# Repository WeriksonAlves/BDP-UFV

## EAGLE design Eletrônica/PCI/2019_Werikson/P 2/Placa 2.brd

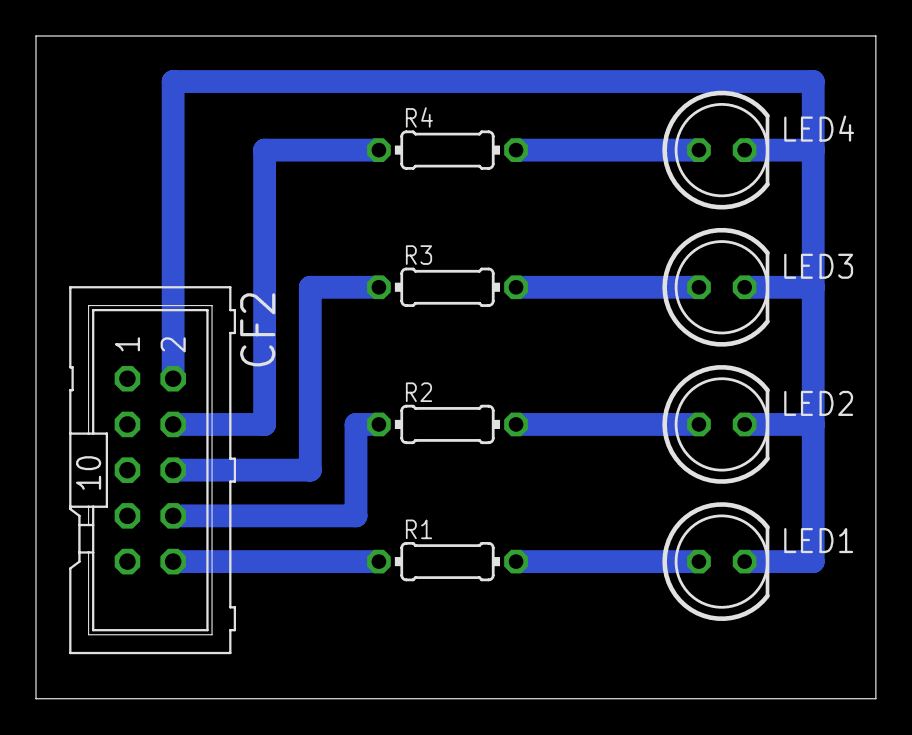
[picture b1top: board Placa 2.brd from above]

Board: 2 copper layers, 46.7 x 36.8 mm, 9 parts (0 on the bottom side), 9 nets.

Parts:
CF2: ML10
LED1, LED2, LED3, LED4: LED5MM
R1, R2, R3, R4: 220; 0204/7

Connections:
GND: CF2.2, LED1.K, LED2.K, LED3.K, LED4.K
unnamed: LED1.A, R1.2
unnamed: LED2.A, R2.2
unnamed: LED3.A, R3.2
unnamed: LED4.A, R4.2
unnamed: CF2.10, R1.1
unnamed: CF2.8, R2.1
unnamed: CF2.6, R3.1
unnamed: CF2.4, R4.1

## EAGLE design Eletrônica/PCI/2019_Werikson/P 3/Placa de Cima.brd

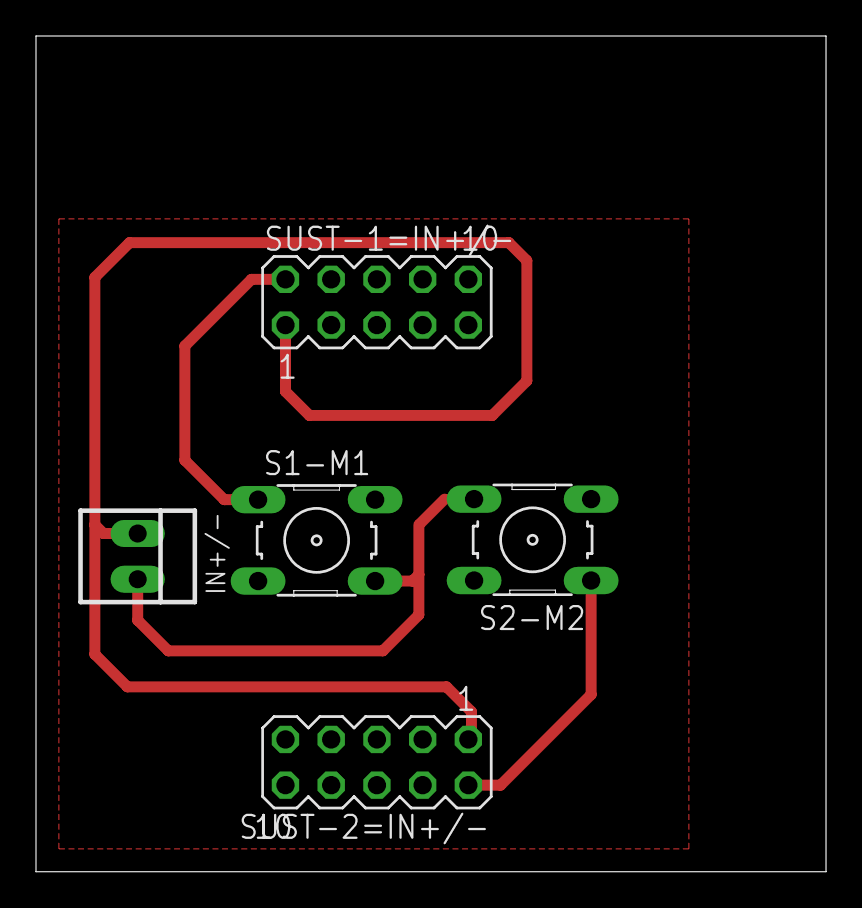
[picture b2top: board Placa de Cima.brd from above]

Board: 2 copper layers, 43.9 x 46.4 mm, 5 parts (0 on the bottom side), 4 nets.

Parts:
IN+/-: 22-23-2021
S1-M1, S2-M2: B3F-10XX
SUST-1=IN+/-, SUST-2=IN+/-: MA05-2

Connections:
GND: IN+/-.1, SUST-1=IN+/-.1, SUST-2=IN+/-.1
unnamed: S1-M1.1, SUST-1=IN+/-.2
unnamed: S2-M2.1, SUST-2=IN+/-.2
unnamed: IN+/-.2, S1-M1.4, S2-M2.4

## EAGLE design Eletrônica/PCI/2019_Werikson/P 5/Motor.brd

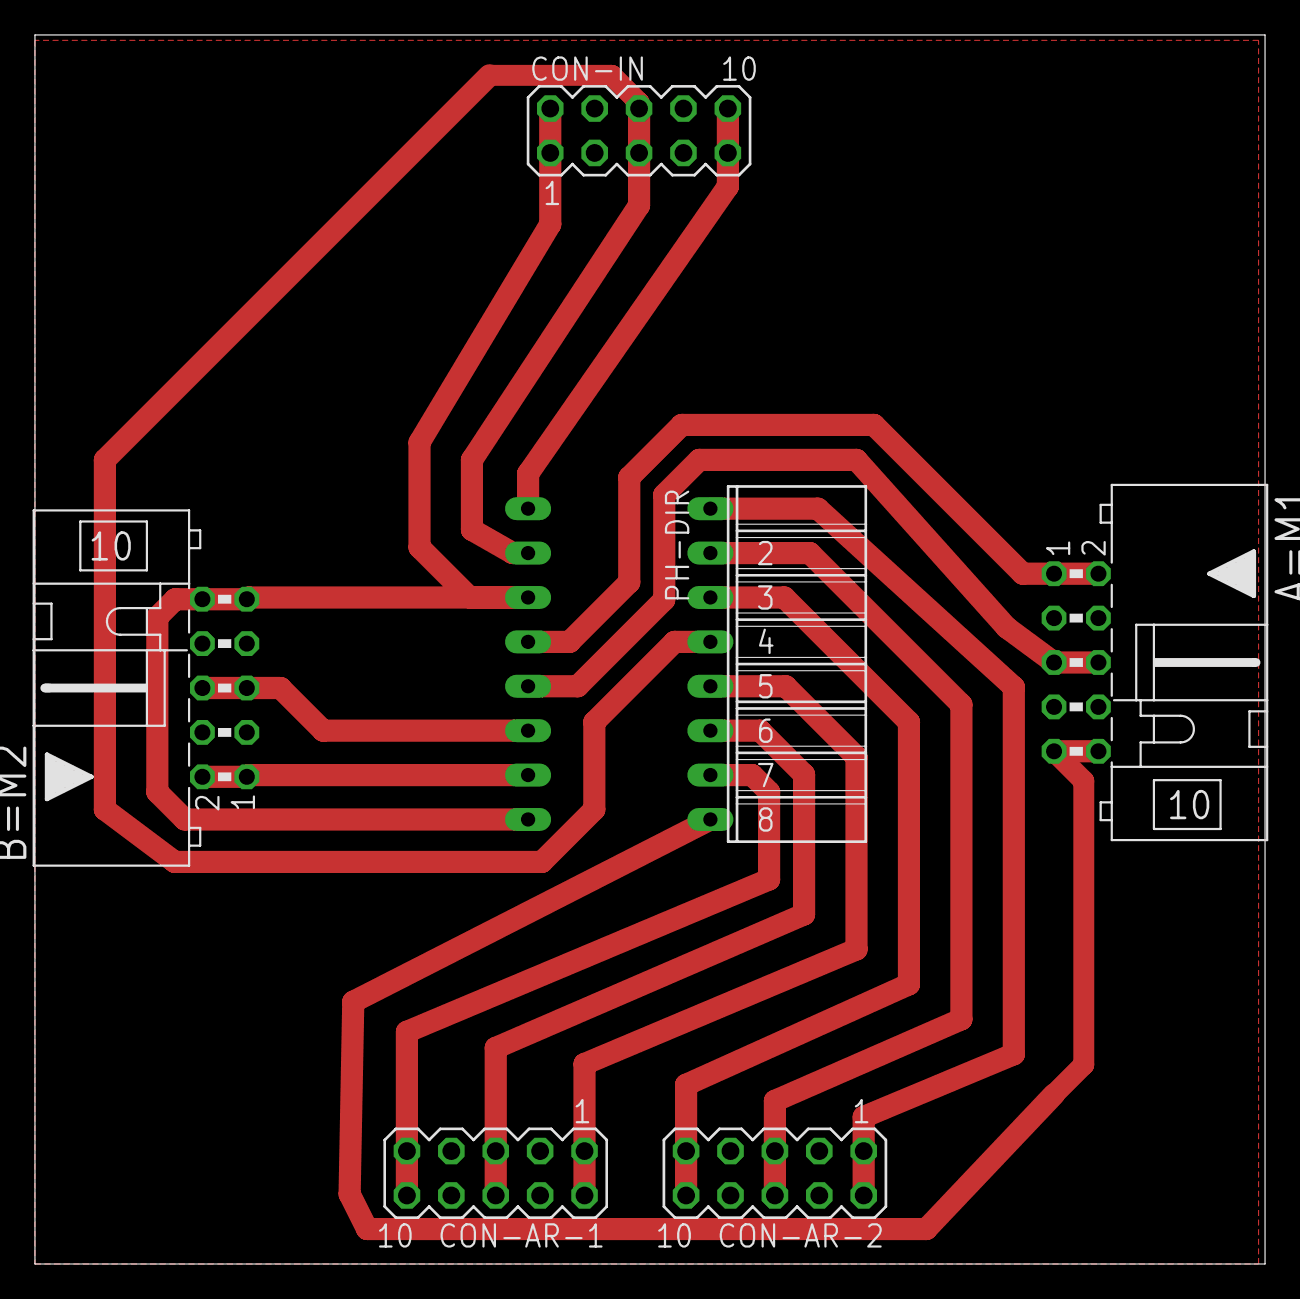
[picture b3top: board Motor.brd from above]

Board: 2 copper layers, 70.4 x 70.3 mm, 7 parts (1 on the bottom side), 13 nets.

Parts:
A=M1: ML10L
B=M2: ML10L
CON-AR-1, CON-AR-2: MA05-2
CON-IN: MA05-2
PH-DIR: FE08W
PH-ESQ: FE08W

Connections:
5V: CON-IN.5, CON-IN.6, PH-DIR.4, PH-ESQ.2
D5: CON-AR-2.1, CON-AR-2.2, PH-DIR.1
D6: CON-AR-1.9, CON-AR-1.10, PH-DIR.7
D7: CON-AR-1.5, CON-AR-1.6, PH-DIR.6
D8: CON-AR-1.1, CON-AR-1.2, PH-DIR.5
GND: A=M1.9, A=M1.10, B=M2.9, B=M2.10, CON-IN.1, CON-IN.2, PH-DIR.8, PH-ESQ.3, PH-ESQ.8
M1-1: A=M1.1, A=M1.2, PH-ESQ.4
M1-2: A=M1.5, A=M1.6, PH-ESQ.5
M2-1: B=M2.1, B=M2.2, PH-ESQ.7
M2-2: B=M2.5, B=M2.6, PH-ESQ.6
RX0: CON-AR-2.5, CON-AR-2.6, PH-DIR.2
TX1: CON-AR-2.9, CON-AR-2.10, PH-DIR.3
V0: CON-IN.9, CON-IN.10, PH-ESQ.1

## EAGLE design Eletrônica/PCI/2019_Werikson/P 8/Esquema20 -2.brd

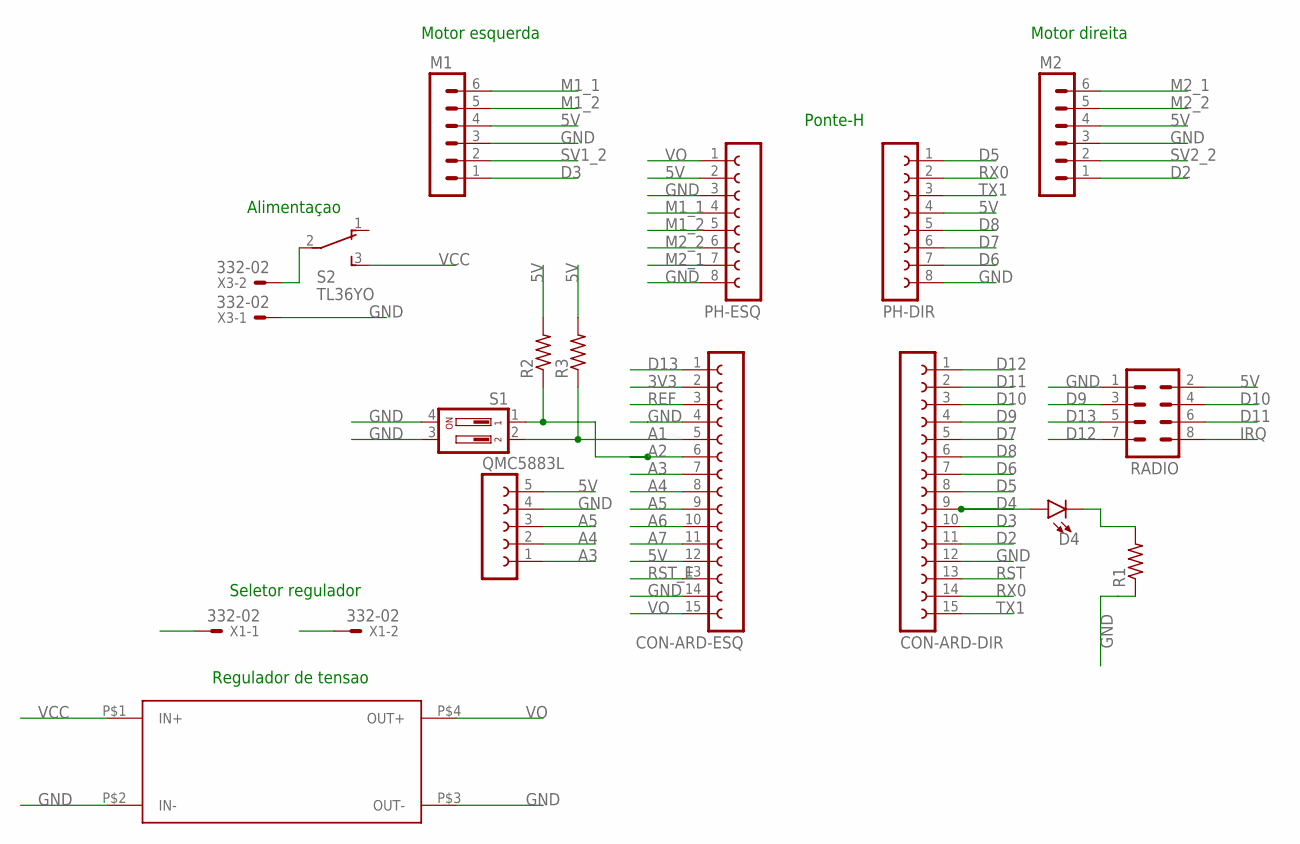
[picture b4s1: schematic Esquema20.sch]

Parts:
CON-ARD-DIR: FE15-1; FE15
CON-ARD-ESQ: FE15-1; FE15
D4: LED-3MM-NO_SILK; LED_3MM-NS
M1, M2: MA06-1
PH-DIR: FE08-1; FE08
PH-ESQ: FE08-1; FE08
QMC5883L: FE05W
R1, R2, R3: R-US_0207/12; 0207/12
RADIO: MA04-2
S1: DA02; DA-02
S2: TL36YO; TL3XYO
U$1: REGULADOR; REGULADOR-FP
X1, X3: 332-02

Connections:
3V3: CON-ARD-ESQ.2
5V: CON-ARD-ESQ.12, M1.4, M2.4, PH-DIR.4, PH-ESQ.2, QMC5883L.5, R2.2, R3.2, RADIO.2
A1: CON-ARD-ESQ.5, R3.1, S1.2
A2: CON-ARD-ESQ.6, R2.1, S1.1
A3: CON-ARD-ESQ.7, QMC5883L.1
A4: CON-ARD-ESQ.8, QMC5883L.2
A5: CON-ARD-ESQ.9, QMC5883L.3
A6: CON-ARD-ESQ.10; also elsewhere on the board
A7: CON-ARD-ESQ.11; also elsewhere on the board
D2: CON-ARD-DIR.11, M2.1
D3: CON-ARD-DIR.10, M1.1
D4: CON-ARD-DIR.9, D4.A
D5: CON-ARD-DIR.8, PH-DIR.1
D6: CON-ARD-DIR.7, PH-DIR.7
D7: CON-ARD-DIR.5, PH-DIR.6
D8: CON-ARD-DIR.6, PH-DIR.5
D9: CON-ARD-DIR.4, RADIO.3
D10: CON-ARD-DIR.3, RADIO.4
D11: CON-ARD-DIR.2, RADIO.6
D12: CON-ARD-DIR.1, RADIO.7
D13: CON-ARD-ESQ.1, RADIO.5
GND: CON-ARD-DIR.12, CON-ARD-ESQ.4, CON-ARD-ESQ.14, M1.3, M2.3, PH-DIR.8, PH-ESQ.3, PH-ESQ.8, QMC5883L.4, R1.1, RADIO.1, S1.3, S1.4, U$1.P$2 (IN-), U$1.P$3 (OUT-), X3.1; also elsewhere on the board
IRQ: RADIO.8
M1_1: M1.6, PH-ESQ.4
M1_2: M1.5, PH-ESQ.5
M2_1: M2.6, PH-ESQ.7
M2_2: M2.5, PH-ESQ.6
unnamed: S2.2, X3.2
unnamed: D4.K (C), R1.2
REF: CON-ARD-ESQ.3
RST: CON-ARD-DIR.13
RST_E: CON-ARD-ESQ.13
RX0: CON-ARD-DIR.14, PH-DIR.2
SV1_2: M1.2
SV2_2: M2.2
TX1: CON-ARD-DIR.15, PH-DIR.3
VCC: S2.3 (S), U$1.P$1 (IN+), X1.1; also elsewhere on the board
VO: CON-ARD-ESQ.15, PH-ESQ.1, U$1.P$4 (OUT+), X1.2

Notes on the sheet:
Motor direita
Motor esquerda
Alimentaçao
Ponte-H
Regulador de tensao
Seletor regulador

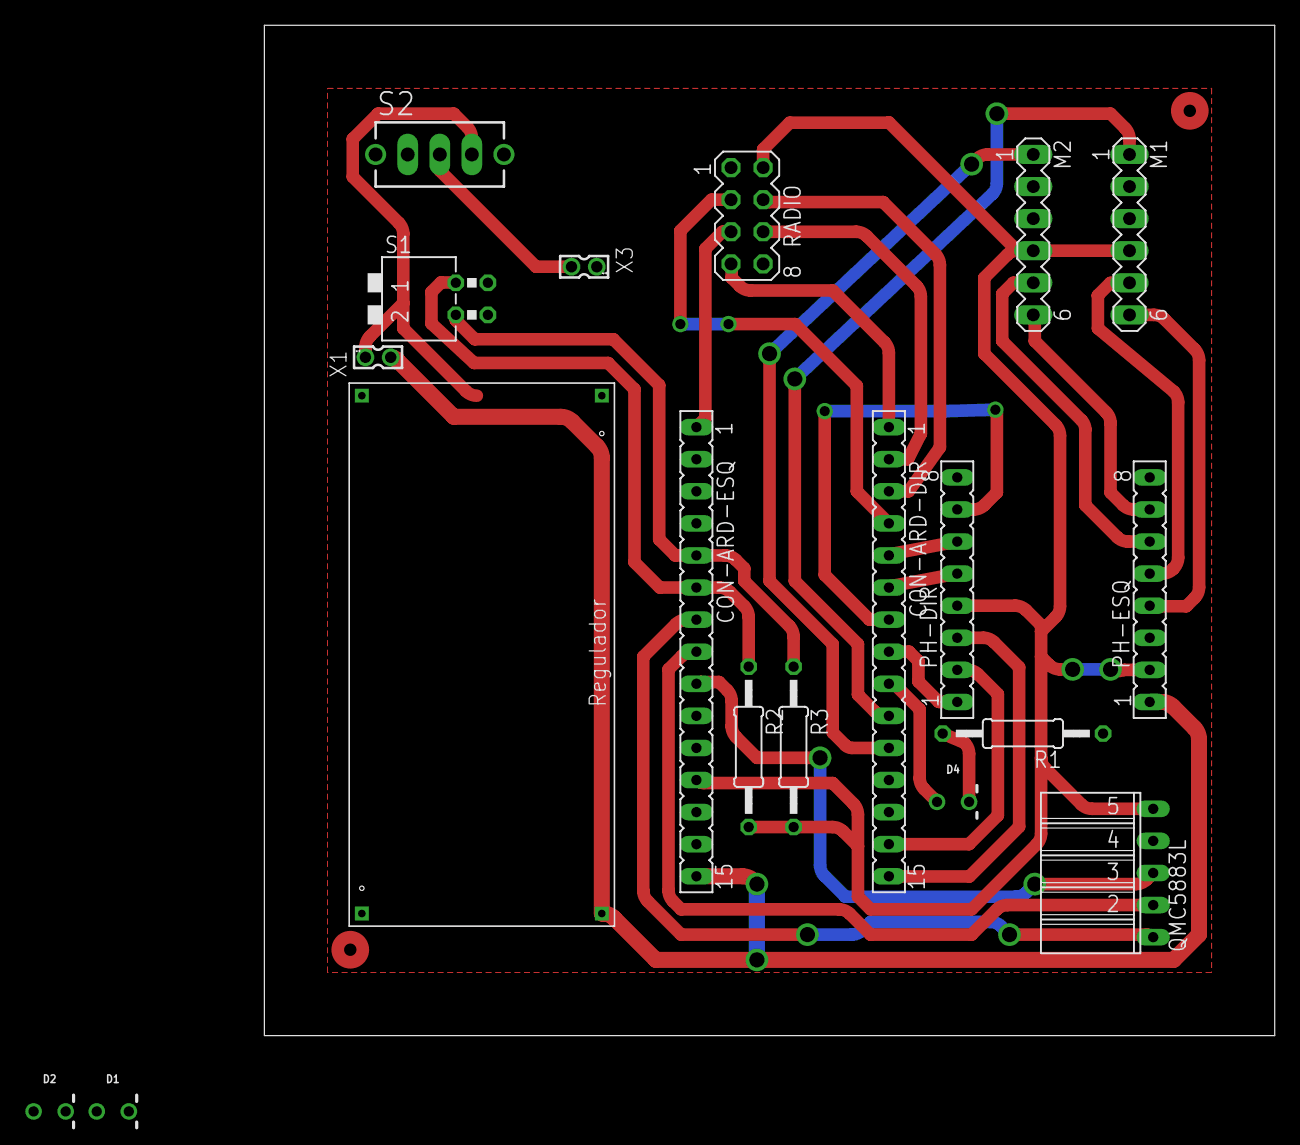
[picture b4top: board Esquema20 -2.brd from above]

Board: 2 copper layers, 80.0 x 80.0 mm, 19 parts (0 on the bottom side), 31 nets.

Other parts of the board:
D1, D2: LED_3MM-NS

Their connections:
A6: D1.K; also elsewhere on the board
A7: D2.A; also elsewhere on the board
GND: D2.K; also elsewhere on the board
VCC: D1.A; also elsewhere on the board

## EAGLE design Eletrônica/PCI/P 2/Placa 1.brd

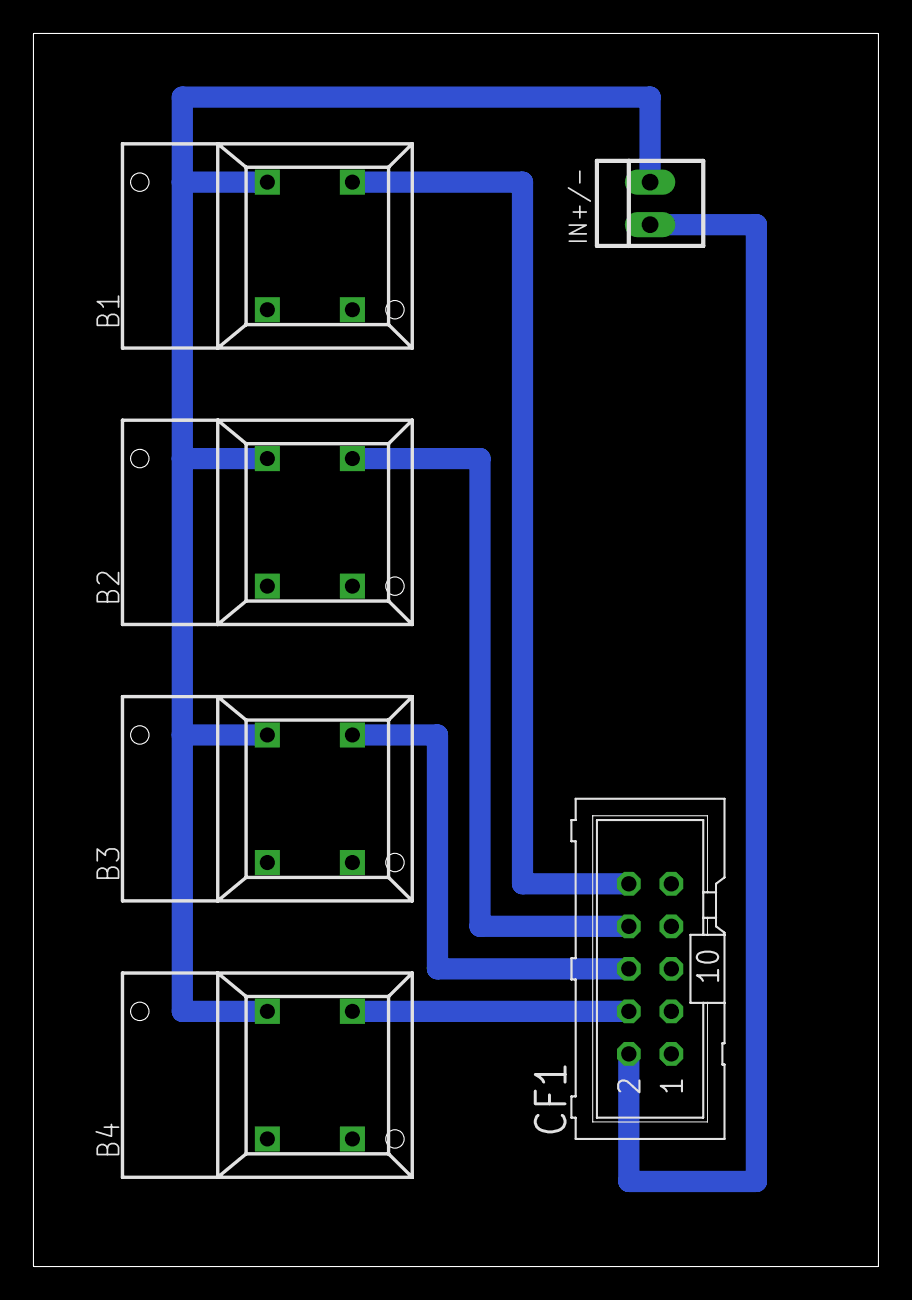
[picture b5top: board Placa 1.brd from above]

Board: 2 copper layers, 50.5 x 73.7 mm, 6 parts (0 on the bottom side), 6 nets.

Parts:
B1, B2, B3, B4: 5501
CF1: ML10
IN+/-: 22-23-2021

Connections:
GND: CF1.2, IN+/-.1
unnamed: B1.1A, B2.1A, B3.1A, B4.1A, IN+/-.2
unnamed: B1.NO, CF1.10
unnamed: B2.NO, CF1.8
unnamed: B3.NO, CF1.6
unnamed: B4.NO, CF1.4

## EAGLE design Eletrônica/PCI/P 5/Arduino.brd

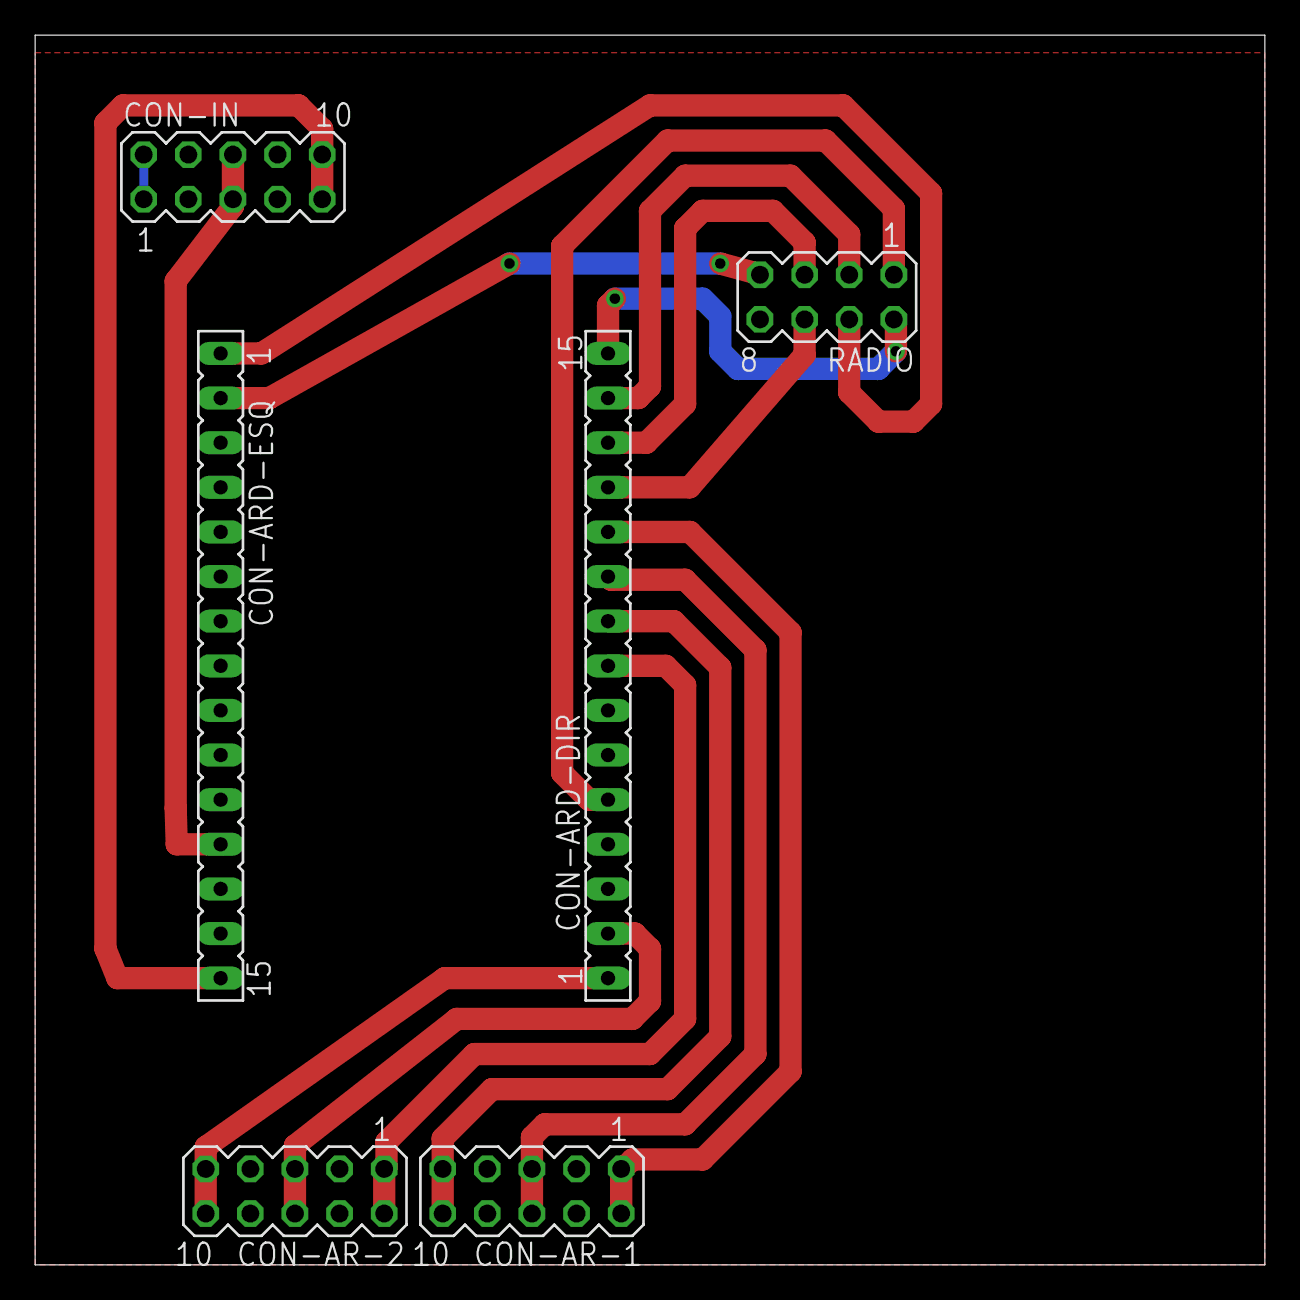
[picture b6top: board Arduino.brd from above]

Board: 2 copper layers, 70.0 x 70.0 mm, 6 parts (0 on the bottom side), 16 nets.

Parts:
CON-AR-1, CON-AR-2: MA05-2
CON-ARD-DIR: FE15
CON-ARD-ESQ: FE15
CON-IN: MA05-2
RADIO: MA04-2

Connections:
3V3: CON-ARD-ESQ.2, RADIO.7
5V: CON-ARD-ESQ.12, CON-IN.5, CON-IN.6
D2: CON-ARD-DIR.5, RADIO.1
D5: CON-AR-2.1, CON-AR-2.2, CON-ARD-DIR.8
D6: CON-AR-1.9, CON-AR-1.10, CON-ARD-DIR.9
D7: CON-AR-1.5, CON-AR-1.6, CON-ARD-DIR.10
D8: CON-AR-1.1, CON-AR-1.2, CON-ARD-DIR.11
D9: CON-ARD-DIR.12, RADIO.6
D10: CON-ARD-DIR.13, RADIO.5
D11: CON-ARD-DIR.14, RADIO.3
D12: CON-ARD-DIR.15, RADIO.2
D13: CON-ARD-ESQ.1, RADIO.4
GND: CON-ARD-DIR.4, CON-ARD-ESQ.14, CON-IN.1, CON-IN.2, RADIO.8
RX0: CON-AR-2.5, CON-AR-2.6, CON-ARD-DIR.2
TX1: CON-AR-2.9, CON-AR-2.10, CON-ARD-DIR.1
VO: CON-ARD-ESQ.15, CON-IN.9, CON-IN.10

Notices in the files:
parts and their libraries:
SparkFun-LED: Licensing: Creative Commons ShareAlike 4.0 International - https://creativecommons.org/licenses/by-sa/4.0
